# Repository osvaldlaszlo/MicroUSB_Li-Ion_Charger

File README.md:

######################################################
#MicroUSB Powered Li-Ion Battery Charger             #
######################################################
http://elegantcircuits.com/2015/03/15/usb-li-ion-battery-charger/

##Bill of Materials:##
* MAX1555EZK+ IC
* MicroUSB Female Adapter
* 2 1uF decoupling capacitors
* Li-Ion Battery

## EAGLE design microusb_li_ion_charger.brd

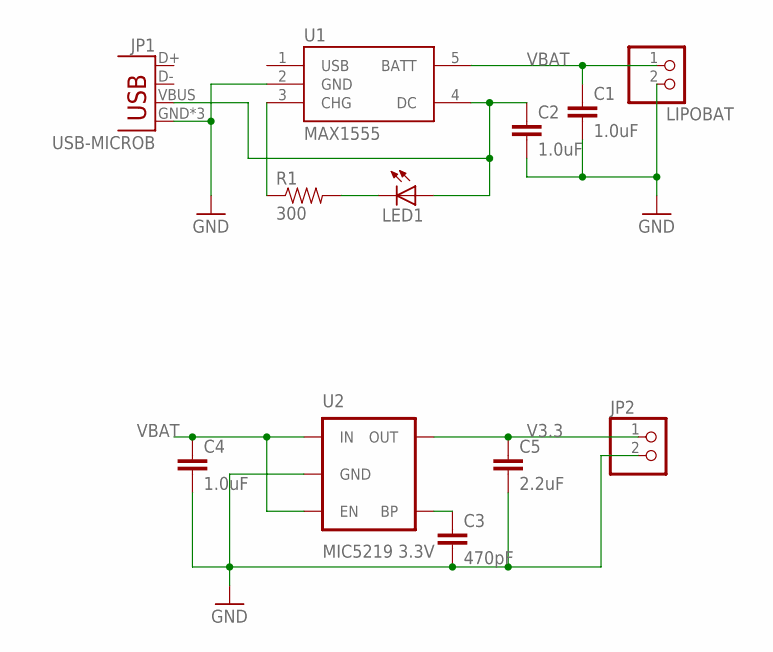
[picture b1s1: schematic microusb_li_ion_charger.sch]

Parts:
C1, C2, C4: 1.0uF; 0805
C3: 470pF; 0805
C5: 2.2uF; 0805
JP1: USB-MICROB
JP2: PINHD-1X2; 1X02
LED1: LEDCHIP-LED0805; CHIP-LED0805
LIPOBAT: JST_2PIN-SMT; JST-PH-2-SMT
R1: 300; 0805
U1: MAX1555; SOT23-5
U2: MIC5219 3.3V; SOT23-5

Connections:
GND: C1.2, C2.2, C3.2, C4.2, C5.2, JP1.GND, JP1.MT1 (GND), JP1.MT2 (GND), JP2.2, LIPOBAT.2 (1), U1.2 (GND), U2.2 (GND)
unnamed: C2.1, JP1.VBUS, LED1.A, U1.4 (DC)
unnamed: R1.1, U1.3 (CHG)
unnamed: LED1.C, R1.2
unnamed: C3.1, U2.4 (BP)
V3.3: C5.1, JP2.1, U2.5 (OUT)
VBAT: C1.1, C4.1, LIPOBAT.1 (2), U1.5 (BATT), U2.1 (IN), U2.3 (EN)

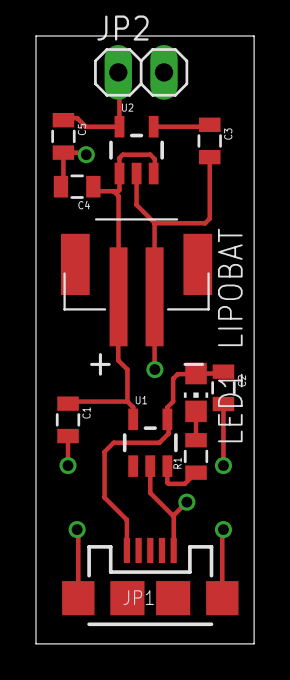
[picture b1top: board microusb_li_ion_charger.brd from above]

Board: 2 copper layers, 12.1 x 33.8 mm, 12 parts (0 on the bottom side), 7 nets.

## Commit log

2015-03-16 add screenshots
2015-08-13 Add LED and 3.3V LDO

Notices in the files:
parts and their libraries:
SparkFun-Capacitors: Licensing: Creative Commons ShareAlike 4.0 International - https://creativecommons.org/licenses/by-sa/4.0
